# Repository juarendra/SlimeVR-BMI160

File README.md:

# SlimeVR-BMI160 DIY Tracker

**SlimeVR-BMI160** adalah proyek tracker full-body DIY (Do It Yourself) berbasis ESP32 dan sensor IMU BMI160, dikembangkan oleh [Positron Electronik](https://www.tokopedia.com/positronelectronic). Solusi ini merupakan alternatif hemat biaya dari tracker SlimeVR original, dengan tetap mempertahankan performa tinggi untuk pengalaman VR yang imersif.

## ⚡ Fitur Unggulan
- **Mikrokontroler**: ESP32-WROOM-32 (WiFi + BLE)
- **Sensor IMU**: BMI160 (header socket, mudah diganti)
- **Manajemen Daya**: USB-C atau LiPo 1S, charger TP4056 + proteksi DW01A
- **Konektor I2C**: Port ekspansi untuk sensor tambahan
- **LED Indikator**: 5 LED untuk status pengisian, koneksi, dan serial
- **Tombol**: Reset & power switch

## 🚀 Cara Penggunaan

### 📦 Isi Paket (untuk produk jadi)
- 1 Unit tracker SlimeVR-BMI160
- 1 Baterai LiPo (terpasang)

### 🔋 Pengisian Daya
- Colokkan USB-C: LED **biru** menyala saat mengisi, **merah** saat penuh.

### 🌐 Flash & Konfigurasi WiFi (Metode Termudah)
Gunakan **Web Installer** tanpa instalasi software:
1. Buka [SlimeVR BMI160 Web Installer](https://juarendra.github.io/SlimeVR-BMI160/) di Chrome/Edge (PC).
2. Hubungkan tracker via USB.
3. Klik **Install Firmware**, lalu masukkan SSID & Password WiFi.
4. Tunggu hingga proses selesai dan tracker terhubung ke server SlimeVR.

> **Catatan**: Web Installer menggunakan Web Serial, jadi pastikan browser mendukung (Chrome/Edge).

### 🛠️ Metode Manual (untuk Developer)
Jika Anda ingin mengembangkan atau mengompilasi firmware sendiri, ikuti panduan lengkap di:
➡️ **[Panduan Flashing Manual](./FIRMWARE/README.md)**

## 📂 Struktur Repositori
| Direktori | Isi |
|-----------|-----|
| `/PCB` | Desain PCB (EAGLE) dan file Gerber |
| `/HARDWARE` | Model 3D case (STL) dan dimensi |
| `/FIRMWARE` | Source code firmware (PlatformIO) dan file .bin compiled |
| `/site` | Web Installer (HTML, CSS, JS, manifest) |
| `/DOC` | Dokumentasi, gambar, BOM, datasheet |
| `/scripts` | Script otomatisasi (QA, release) |

## 🔧 Untuk Pengembang (DIY)
Jika Anda ingin merakit sendiri:
1. **Rakit Hardware**: Gunakan file PCB dari `/PCB/CAD-CAM`, BOM dari `/DOC/BOM_SlimeVRDiyModular.csv`, dan case 3D dari `/HARDWARE/case`.
2. **Flash Firmware**: Ikuti panduan di `/FIRMWARE/README.md`.
3. **Verifikasi**: Gunakan serial monitor untuk memastikan koneksi WiFi dan sensor.

## 🐛 Pemecahan Masalah Umum
- **Tracker tidak muncul di server**: Pastikan SSID/password benar, PC dan tracker satu jaringan, saklar ON.
- **LED mati total**: Cek saklar, charge baterai via USB-C.

## 📖 Dokumentasi Lengkap
- [Dokumentasi Software (PDF)](./DOC/SOFTWARE_USAGE.pdf) — panduan detail penggunaan web installer dan manual.

<details>
<summary><strong>📐 Detail Teknis dan Galeri</strong></summary>

| Fitur | Komponen |
|-------|----------|
| Mikrokontroler | ESP32-WROOM-32 |
| Sensor IMU | BMI160 |
| USB-to-Serial | FTDI FT231XS |
| Charger | TP4056 |
| Proteksi Baterai | DW01A + FS8205A |
| Regulator | M3406 (3.3V 800mA) |

**Diagram Pinout**:

**Dimensi Board**: [PDF](https://github.com/juarendra/SlimeVR-BMI160/blob/main/HARDWARE/dimension_SlimeVR.pdf)

**Galeri**:

</details>

## ❓ FAQ
*Segera hadir.*

## 🤝 Kontribusi
Pull request dan saran sangat diterima! Silakan buka issue di GitHub.

## 📜 Lisensi
MIT License © 2024 Positron Electronik

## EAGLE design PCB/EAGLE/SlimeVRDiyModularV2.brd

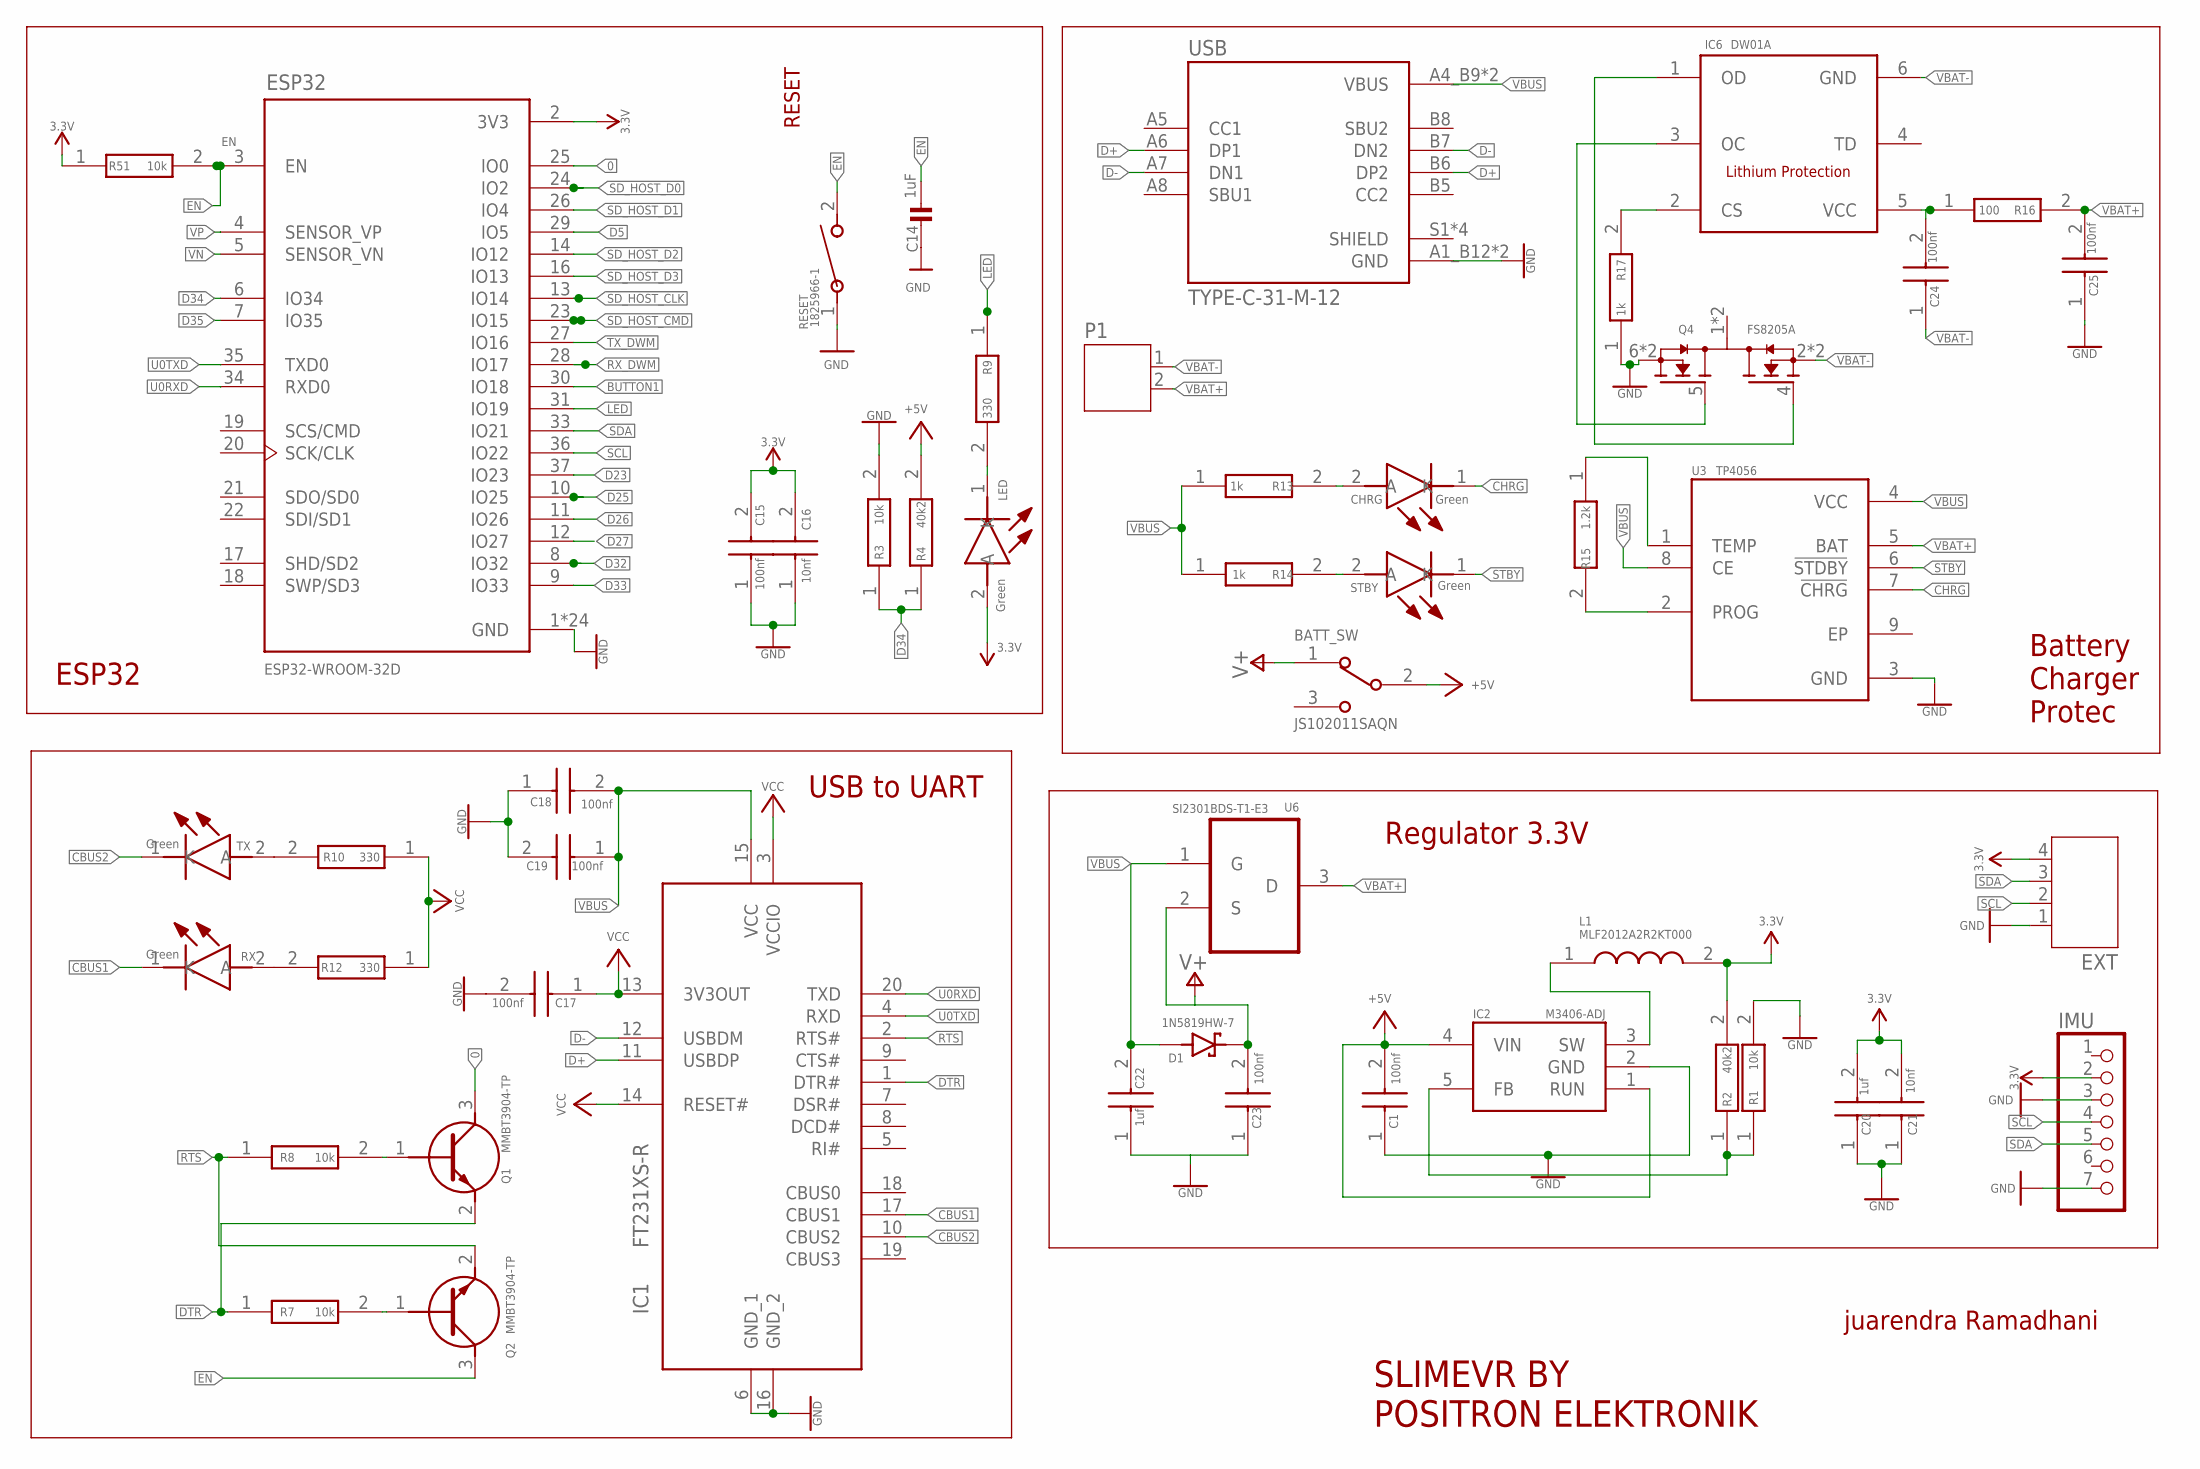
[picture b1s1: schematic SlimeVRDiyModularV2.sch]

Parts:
BATT_SW: JS102011SAQN; SW_JS102011SAQN
C1, C15, C17, C18, C19, C23, C24, C25: 100nf; CAPC1608X87N
C14: 1uF; 0603
C16, C21: 10nf; CAPC1608X87N
C20, C22: 1uf; CAPC1608X87N
CHRG: Green; LEDC2012X80N
D1: 1N5819HW-7; SOD3715X145N
ESP32: ESP32-WROOM-32D; MODULE_ESP32-WROOM-32D
EXT: JST-PH4
IC1: FT231XS-R; SOP64P599X175-20N
IC2: M3406-ADJ; SOT95P280X100-5N
IC6: DW01A; SOT23-6
IMU: PINHD-1X7; 1X07
L1: MLF2012A2R2KT000; INDC2012X105N
LED: Green; LEDC2012X80N
P1: JST-PH2
Q1, Q2: MMBT3904-TP; SI2305TP
Q4: FS8205A; SOP65P640X120-8N
R1, R3, R7, R8, R51: 10k; RESC1608X55N
R2, R4: 40k2; RESC1608X55N
R9, R10, R12: 330; ERJH3
R13, R14, R17: 1k; RESC1608X55N
R15: 1.2k; RESC1608X55N
R16: 100; RESC1608X55N
RESET: 1825966-1; SWDIP2_256X170P100
RX: Green; LEDC2012X80N
STBY: Green; LEDC2012X80N
TX: Green; LEDC2012X80N
U3: TP4056; SOP127P600X175-9N
U6: SI2301BDS-T1-E3; SOT95P237X112-3N
USB: TYPE-C-31-M-12; HRO_TYPE-C-31-M-12

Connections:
0: ESP32.25 (IO0), Q1.3 (C)
3.3V: C15.2, C16.2, C20.2, C21.2, ESP32.2 (3V3), EXT.4, IMU.2, L1.2, LED.2 (A), R2.2, R51.1
+5V: BATT_SW.2, C1.2, IC2.1 (RUN), IC2.4 (VIN), R4.2
BUTTON1: ESP32.30 (IO18)
CBUS1: IC1.17 (CBUS1), RX.1 (K)
CBUS2: IC1.10 (CBUS2), TX.1 (K)
CHRG: CHRG.1 (K), U3.7 (!CHRG)
D5: ESP32.29 (IO5)
D23: ESP32.37 (IO23)
D25: ESP32.10 (IO25)
D26: ESP32.11 (IO26)
D27: ESP32.12 (IO27)
D32: ESP32.8 (IO32)
D33: ESP32.9 (IO33)
D34: ESP32.6 (IO34), R3.1, R4.1
D35: ESP32.7 (IO35)
D+: IC1.11 (USBDP), USB.A6 (DP1), USB.B6 (DP2)
D-: IC1.12 (USBDM), USB.A7 (DN1), USB.B7 (DN2)
DTR: IC1.1 (DTR#), Q1.2 (E), R7.1
EN: C14.1, ESP32.3 (EN), Q2.3 (C), R51.2, RESET.2
GND: C1.1, C14.2, C15.1, C16.1, C17.2, C18.1, C19.2, C20.1, C21.1, C22.1, C23.1, C25.1, ESP32.1 (GND), ESP32.15 (GND), ESP32.38 (GND), ESP32.39_1 (GND), ESP32.39_2 (GND), ESP32.39_3 (GND), ESP32.39_4 (GND), ESP32.39_5 (GND), ESP32.39_6 (GND), ESP32.39_7 (GND), ESP32.39_8 (GND), ESP32.39_9 (GND), ESP32.39_10 (GND), ESP32.39_11 (GND), ESP32.39_12 (GND), ESP32.39_13 (GND), ESP32.39_14 (GND), ESP32.39_15 (GND), ESP32.39_16 (GND), ESP32.39_17 (GND), ESP32.39_18 (GND), ESP32.39_19 (GND), ESP32.39_20 (GND), ESP32.39_21 (GND), EXT.1, IC1.6 (GND_1), IC1.16 (GND_2), IC2.2 (GND), IMU.3, IMU.7, Q4.6 (S2), Q4.7 (S2), R1.2, R3.2, R17.1, RESET.1, U3.3 (GND), USB.A1_B12 (GND), USB.B1_A12 (GND)
LED: ESP32.31 (IO19), R9.1
unnamed: IC2.3 (SW), L1.1
unnamed: LED.1 (K), R9.2
unnamed: IC2.5 (FB), R1.1, R2.1
unnamed: Q2.1 (B), R7.2
unnamed: Q1.1 (B), R8.2
unnamed: R12.2, RX.2 (A)
unnamed: R10.2, TX.2 (A)
unnamed: CHRG.2 (A), R13.2
unnamed: R14.2, STBY.2 (A)
unnamed: R15.1, U3.1 (TEMP)
unnamed: R15.2, U3.2 (PROG)
unnamed: C24.2, IC6.5 (VCC), R16.1
unnamed: IC6.1 (OD), Q4.4 (G1)
unnamed: IC6.2 (CS), R17.2
unnamed: IC6.3 (OC), Q4.5 (G2)
RTS: IC1.2 (RTS#), Q2.2 (E), R8.1
RX_DWM: ESP32.28 (IO17)
SCL: ESP32.36 (IO22), EXT.2, IMU.4
SDA: ESP32.33 (IO21), EXT.3, IMU.5
SD_HOST_CLK: ESP32.13 (IO14)
SD_HOST_CMD: ESP32.23 (IO15)
SD_HOST_D0: ESP32.24 (IO2)
SD_HOST_D1: ESP32.26 (IO4)
SD_HOST_D2: ESP32.14 (IO12)
SD_HOST_D3: ESP32.16 (IO13)
STBY: STBY.1 (K), U3.6 (!STDBY)
TX_DWM: ESP32.27 (IO16)
U0RXD: ESP32.34 (RXD0), IC1.20 (TXD)
U0TXD: ESP32.35 (TXD0), IC1.4 (RXD)
V+: BATT_SW.1, C23.2, D1.C (K), U6.2 (S)
VBAT+: C25.2, P1.2, R16.2, U3.5 (BAT), U6.3 (D)
VBAT-: C24.1, IC6.6 (GND), P1.1, Q4.2 (S1), Q4.3 (S1)
VBUS: C18.2, C19.1, C22.2, D1.A, IC1.15 (VCC), R13.1, R14.1, U3.4 (VCC), U3.8 (CE), U6.1 (G), USB.A4_B9 (VBUS), USB.B4_A9 (VBUS)
VCC: C17.1, IC1.3 (VCCIO), IC1.13 (3V3OUT), IC1.14 (RESET#), R10.1, R12.1
VN: ESP32.5 (SENSOR_VN)
VP: ESP32.4 (SENSOR_VP)

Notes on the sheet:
RESET
ESP32
USB to UART
Battery Charger Protec
Regulator 3.3V
SLIMEVR BY POSITRON ELEKTRONIK
juarendra Ramadhani

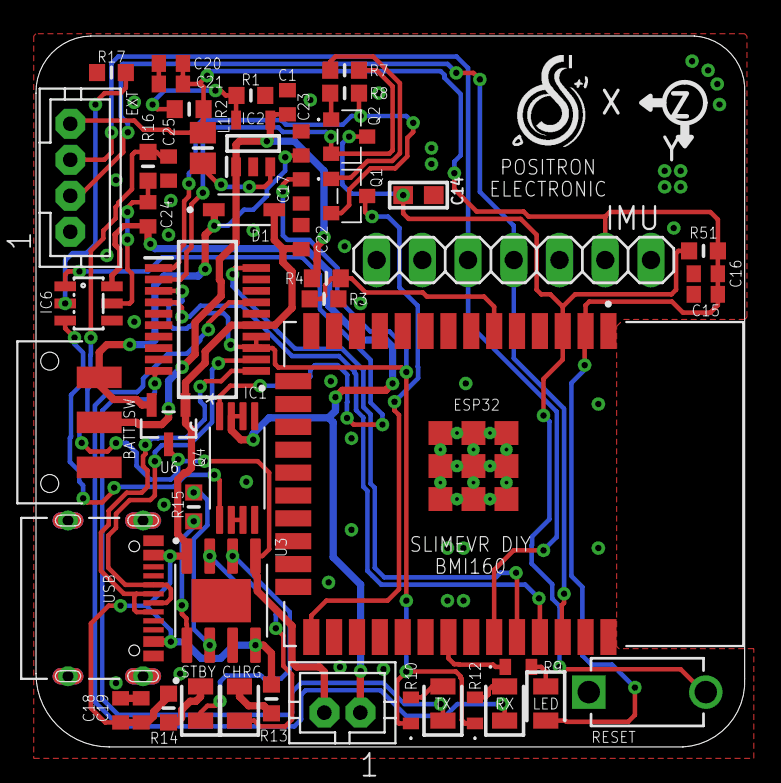
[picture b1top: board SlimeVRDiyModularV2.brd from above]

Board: 2 copper layers, 39.4 x 39.5 mm, 50 parts (0 on the bottom side), 39 nets.

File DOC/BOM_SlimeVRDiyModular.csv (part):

"Qty";"Value";"Device";"Package";"Parts";"Description";"AVAILABILITY";"BUILT_BY";"CATEGORY";"CHECK_PRICES";"COPYRIGHT";"DESCRIPTION";"DIGIKEY_PARTNUMBER";"DIGIKEY_PRICE-STOCK";"HEIGHT";"LCSC_PART_NUMBER";"LCSC_PRICE-STOCK";"MANUFACTURER_NAME";"MANUFACTURER_PART_NUMBER";"MF";"MOUSER_PART_NUMBER";"MOUSER_PRICE-STOCK";"MP";"PACKAGE";"PART_STATUS";"POPULARITY";"PRICE";"PURCHASE-URL";"SERIES";"SNAPEDA_LINK";"VALUE";"VENDOR";
"1";"";"JST-PH2";"JST-PH2";"P1";"";"";"";"";"";"";"";"";"";"";"";"";"";"";"";"";"";"";"";"";"";"";"";"";"";"";"";
"1";"";"JST-PH4";"JST-PH4";"EXT";"";"";"";"";"";"";"";"";"";"";"";"";"";"";"";"";"";"";"";"";"";"";"";"";"";"";"";
"1";"";"PINHD-1X7";"1X07";"IMU";"PIN HEADER";"";"";"";"";"";"";"";"";"";"";"";"";"";"";"";"";"";"";"";"0";"";"";"";"";"";"";
"1";"1.2k";"ESR03EZPJ102";"RESC1608X55N";"R15";"Thick Film Resistors - SMD 0603 1Kohm 5% Anti Surge AEC-Q200";"";"";"";"";"";"Thick Film Resistors - SMD 0603 1Kohm 5% Anti Surge AEC-Q200";"RHM1.0KDCT-ND";"https://www.digikey.com/product-detail/en/rohm-semiconductor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";"0.55mm";"";"";"ROHM Semiconductor";"ESR03EZPJ102";"";"755-ESR03EZPJ102";"https://www.mouser.co.uk/ProductDetail/ROHM-Semiconductor/ES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";"";"";"";"";"";"";"";"";"1k";"";
"1";"100";"ESR03EZPJ102";"RESC1608X55N";"R16";"Thick Film Resistors - SMD 0603 1Kohm 5% Anti Surge AEC-Q200";"";"";"";"";"";"Thick Film Resistors - SMD 0603 1Kohm 5% Anti Surge AEC-Q200";"RHM1.0KDCT-ND";"https://www.digikey.com/product-detail/en/rohm-semiconductor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";"0.55mm";"";"";"ROHM Semiconductor";"ESR03EZPJ102";"";"755-ESR03EZPJ102";"https://www.mouser.co.uk/ProductDetail/ROHM-Semiconductor/ES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";"";"";"";"";"";"";"";"";"1k";"";
"8";"100nf";"885012206071";"CAPC1608X87N";"C1, C15, C17, C18, C19, C23, C24, C25";"Wurth Elektronik 0603 WCAP-CSGP 100nF Ceramic Multilayer Capacitor, 25 V dc, +125C, X7R Dielectric, +/-10%";"";"";"";"";"";"Wurth Elektronik 0603 WCAP-CSGP 100nF Ceramic Multilayer Capacitor, 25 V dc, +125C, X7R Dielectric, +/-10%";"732-7989-1-ND";"https://www.digikey.com/product-detail/en/w%C3%BCrth-elektro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";"0.87mm";"";"";"Wurth Elektronik";"885012206071";"";"710-885012206071";"https://www.mouser.co.uk/ProductDetail/Wurth-Elektronik/8850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";"";"";"";"";"";"";"";"";"100nf";"";
"5";"10k";"ESR03EZPJ103";"RESC1608X55N";"R1, R3, R7, R8, R51";"Thick Film Resistors - SMD 0603 10Kohm 5% Anti Surge AEC-Q200";"";"";"";"";"";"Thick Film Resistors - SMD 0603 10Kohm 5% Anti Surge AEC-Q200";"RHM10KDCT-ND";"https://www.digikey.com/product-detail/en/rohm-semiconductor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";"0.55mm";"";"";"ROHM Semiconductor";"ESR03EZPJ103";"";"755-ESR03EZPJ103";"https://www.mouser.com/Search/Refine.aspx?Keyword=755-ESR03EZPJ103";"";"";"";"";"";"";"";"";"10k";"";
"2";"10nf";"885012206089";"CAPC1608X87N";"C16, C21";"Wurth Elektronik 0603 WCAP-CSGP 10nF Ceramic Multilayer Capacitor, 50 V dc, +125C, X7R Dielectric, +/-10%";"";"";"";"";"";"Wurth Elektronik 0603 WCAP-CSGP 10nF Ceramic Multilayer Capacitor, 50 V dc, +125C, X7R Dielectric, +/-10%";"732-8007-1-ND";"https://www.digikey.com/product-detail/en/w%C3%BCrth-elektro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";"0.87mm";"";"";"Wurth Elektronik";"885012206089";"";"710-885012206089";"https://www.mouser.co.uk/ProductDetail/Wurth-Elektronik/8850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";"";"";"";"";"";"";"";"";"10nf";"";
"1";"1825966-1";"1825966-1";"SWDIP2_256X170P100";"RESET";"";"";"EMA_UL_Team";"Tactile Switches";"";"Copyright (C) 2016 Accelerated Designs. All rights reserved";"FSMCH=3.5 X 6.0 X 4.3 TACT SWITCH, HT";"";"";"";"";"";"";"1825966-1";"";"";"";"";"";"active";"";"";"";"Unknown";"";"";"TE Connectivity";
"1";"1N5819HW-7";"1N5819HW-7";"SOD3715X145N";"D1";"1N5819HW Series 40 V 1 A Surface Mount Schottky Barrier Rectifier - SOD-123  Check availability";"In Stock";"";"";"https://www.snapeda.com/parts/1N5819HW-7/Diodes+Inc./view-pa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";"";" Diode Schottky 40 V 1A Surface Mount SOD-123 ";"";"";"";"";"";"";"";"Diodes Inc.";"";"";"1N5819HW-7";"SOD-123 Fairchild Semiconductor";"";"";"None";"https://www.snapeda.com/api/url_track_click_mouser/?unipart_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 Inc.&part_name=1N5819HW-7&search_term=1n5819 ";"";"https://www.snapeda.com/parts/1N5819HW-7/Diodes+Inc./view-pa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";"";"";
"3";"1k";"ESR03EZPJ102";"RESC1608X55N";"R13, R14, R17";"Thick Film Resistors - SMD 0603 1Kohm 5% Anti Surge AEC-Q200";"";"";"";"";"";"Thick Film Resistors - SMD 0603 1Kohm 5% Anti Surge AEC-Q200";"RHM1.0KDCT-ND";"https://www.digikey.com/product-detail/en/rohm-semiconductor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";"0.55mm";"";"";"ROHM Semiconductor";"ESR03EZPJ102";"";"755-ESR03EZPJ102";"https://www.mouser.co.uk/ProductDetail/ROHM-Semiconductor/ES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";"";"";"";"";"";"";"";"";"1k";"";
"1";"1uF";"CAP_CERAMIC0603";"0603";"C14";"Ceramic Capacitors";"";"";"";"";"";"";"";"";"";"";"";"";"";"";"";"";"";"";"";"";"";"";"";"";"";"";
"2";"1uf";"885012206071";"CAPC1608X87N";"C20, C22";"Wurth Elektronik 0603 WCAP-CSGP 100nF Ceramic Multilayer Capacitor, 25 V dc, +125C, X7R Dielectric, +/-10%";"";"";"";"";"";"Wurth Elektronik 0603 WCAP-CSGP 100nF Ceramic Multilayer Capacitor, 25 V dc, +125C, X7R Dielectric, +/-10%";"732-7989-1-ND";"https://www.digikey.com/product-detail/en/w%C3%BCrth-elektro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";"0.87mm";"";"";"Wurth Elektronik";"885012206071";"";"710-885012206071";"https://www.mouser.co.uk/ProductDetail/Wurth-Elektronik/8850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";"";"";"";"";"";"";"";"";"100nf";"";
"3";"330";"ERJ-H3EF3300V";"ERJH3";"R9, R10, R12";"Power Rating 0.125W,Resistance 330 Ohm,LxW(EIA) 1.6 x 0.8 (EIA:0603) mm";"";"";"";"";"";"Power Rating 0.125W,Resistance 330 Ohm,LxW(EIA) 1.6 x 0.8 (EIA:0603) mm";"";"";"mm";"";"";"Panasonic";"ERJ-H3EF3300V";"";"667-ERJ-H3EF3300V";"https://www.mouser.co.uk/ProductDetail/Panasonic/ERJ-H3EF330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";"";"";"";"";"";"";"";"";"330";"";
"2";"40k2";"ERJ-S03F4022V";"RESC1608X55N";"R2, R4";"Thick Film Resistors - SMD 0603 40.2Kohms 1% Anti-Sulfur";"";"";"";"";"";"Thick Film Resistors - SMD 0603 40.2Kohms 1% Anti-Sulfur";"";"";"0.55mm";"";"";"Panasonic";"ERJ-S03F4022V";"";"667-ERJ-S03F4022V";"https://www.mouser.com/Search/Refine.aspx?Keyword=667-ERJ-S03F4022V";"";"";"";"";"";"";"";"";"";"";
"1";"DW01A";"DW01A";"SOT23-6";"IC6";"Check availability";"Not in stock";"";"";"https://www.snapeda.com/parts/DW01A/Fortune+Semiconductor/vi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";"";" One Cell Lithium-ion/Polymer Battery Protection IC ";"";"";"";"";"";"";"";"Fortune Semiconductor";"";"";"DW01A";"SOT-23-6 Fortune Semiconductor";"";"";"None";"";"";"https://www.snapeda.com/parts/DW01A/Fortune+Semiconductor/vi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";"";"";
"1";"ESP32-WROOM-32D";"ESP32-WROOM-32D";"MODULE_ESP32-WROOM-32D";"ESP32";"Bluetooth, WiFi 802.11b/g/n, Bluetooth v4.2 + EDR, Class 1, 2 and 3 Transceiver Module 2.4GHz ~ 2.5GHz Integrated, Trace Surface Mount Check availability";"In Stock";"";"";"";"";" Bluetooth, WiFi 802.11b/g/n, Bluetooth v4.2 +EDR, Class 1, 2 and 3 Transceiver Module 2.4GHz ~ 2.5GHz Integrated ";"";"";"";"";"";"";"";"Espressif Systems";"";"";"ESP32-WROOM-32D";"Module Espressif Systems";"";"";"None";"https://pricing.snapeda.com/search/part/ESP32-WROOM-32D/?ref=eda";"";"";"";"";
"1";"FS8205A";"FS8205A";"SOP65P640X120-8N";"Q4";"N/A Check availability";"Not in stock";"";"";"https://www.snapeda.com/parts/FS8205A/Fortune+Semiconductor/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";"";" ";"";"";"";"";"";"";"";"Fortune Semiconductor";"";"";"FS8205A";"Package ";"";"";"None";"";"";"https://www.snapeda.com/parts/FS8205A/Fortune+Semiconductor/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";"";"";
"1";"FT231XS-R";"FT231XS-R";"SOP64P599X175-20N";"IC1";"FTDI Chip FT231XS-R, Interface RS232, RS422, RS485, SIE, UART 3MBd, 5 V, 20-pin, SSOP";"";"";"";"";"";"FTDI Chip FT231XS-R, Interface RS232, RS422, RS485, SIE, UART 3MBd, 5 V, 20-pin, SSOP";"";"";"1.753mm";"";"";"FTDI Chip";"FT231XS-R";"";"895-FT231XS-R";"https://www.mouser.co.uk/ProductDetail/FTDI/FT231XS-R?qs=Gp1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";"";"";"";"";"";"";"";"";"";"";
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
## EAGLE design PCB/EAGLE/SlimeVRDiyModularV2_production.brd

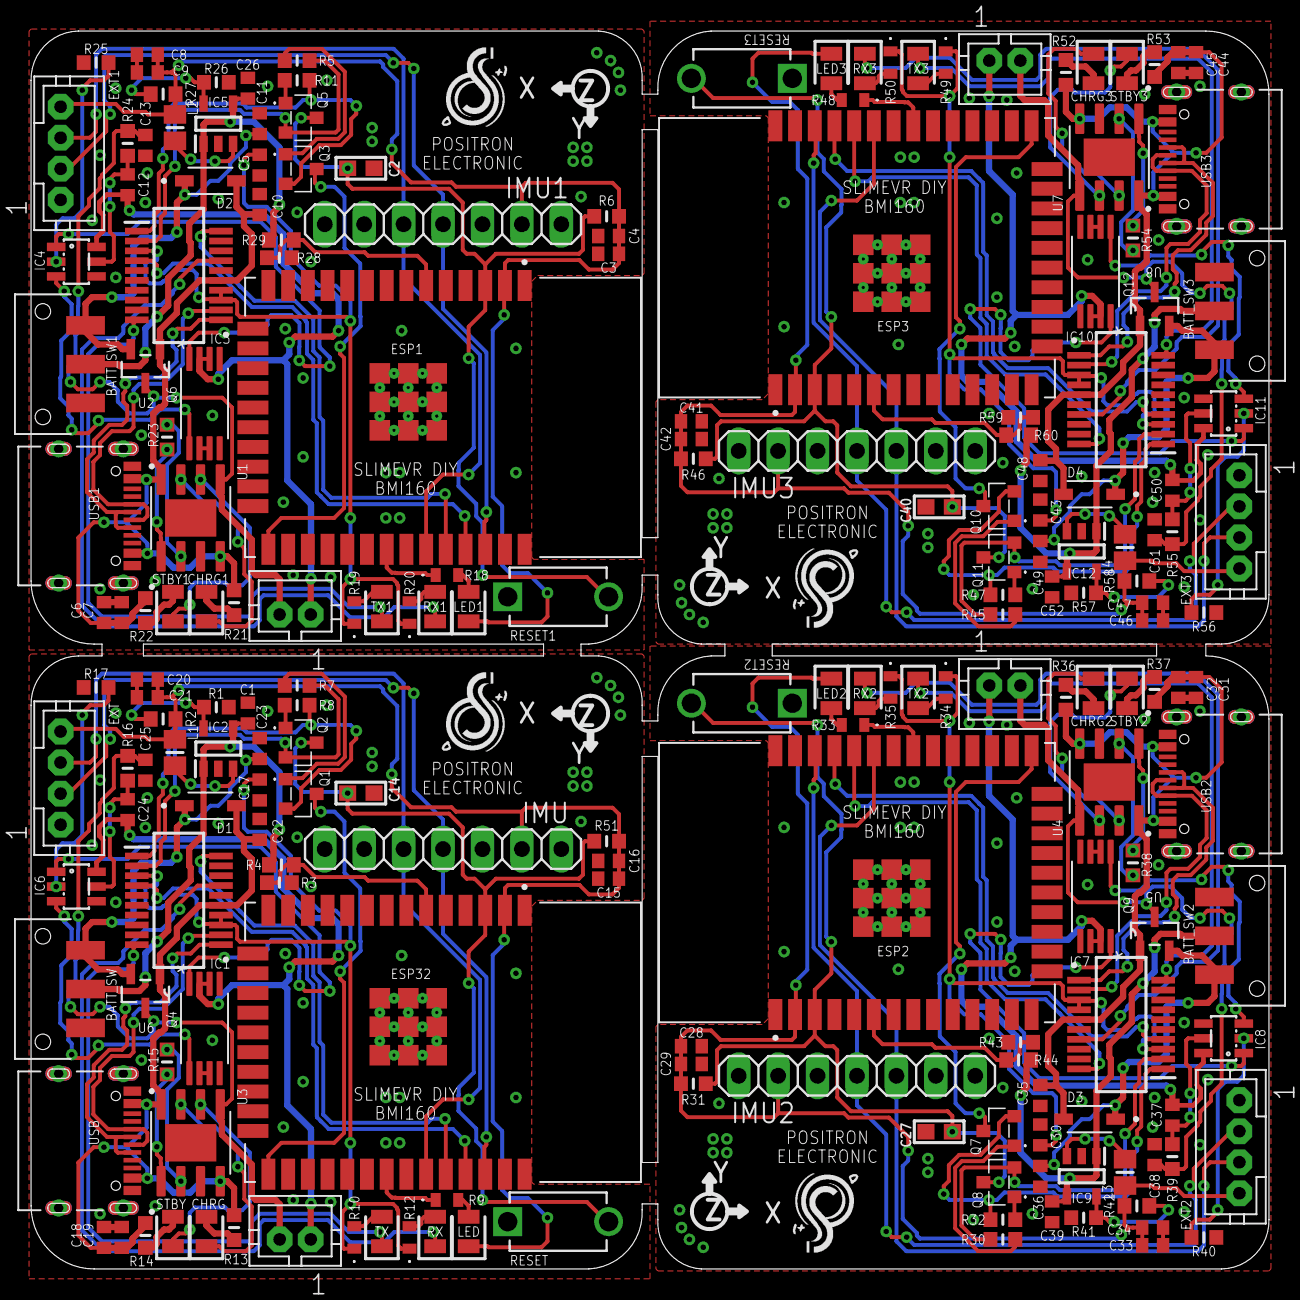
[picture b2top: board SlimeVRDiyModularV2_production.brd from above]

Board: 2 copper layers, 79.8 x 79.8 mm, 200 parts (0 on the bottom side), 156 nets.

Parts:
BATT_SW, BATT_SW1, BATT_SW2, BATT_SW3: JS102011SAQN; SW_JS102011SAQN
C1, C3, C5, C6, C7, C11, C12, C13, C15, C17, C18, C19, C23, C24, C25, C26, C28, C30, C31, C32, C36, C37, C38, C39, C41, C43, C44, C45, C49, C50, C51, C52: 100nf; CAPC1608X87N
C2, C14, C27, C40: 1uF; 0603
C4, C9, C16, C21, C29, C34, C42, C47: 10nf; CAPC1608X87N
C8, C10, C20, C22, C33, C35, C46, C48: 1uf; CAPC1608X87N
CHRG, CHRG1, CHRG2, CHRG3: Green; LEDC2012X80N
D1, D2, D3, D4: 1N5819HW-7; SOD3715X145N
ESP1, ESP2, ESP3, ESP32: ESP32-WROOM-32D; MODULE_ESP32-WROOM-32D
EXT, EXT1, EXT2, EXT3: JST-PH4
IC1, IC3, IC7, IC10: FT231XS-R; SOP64P599X175-20N
IC2, IC5, IC9, IC12: M3406-ADJ; SOT95P280X100-5N
IC4, IC6, IC8, IC11: DW01A; SOT23-6
IMU, IMU1, IMU2, IMU3: 1X07
L1, L2, L3, L4: MLF2012A2R2KT000; INDC2012X105N
LED, LED1, LED2, LED3: Green; LEDC2012X80N
P1, P2, P3, P4: JST-PH2
Q1, Q2, Q3, Q5, Q7, Q8, Q10, Q11: MMBT3904-TP; SI2305TP
Q4, Q6, Q9, Q12: FS8205A; SOP65P640X120-8N
R1, R3, R5, R6, R7, R8, R11, R26, R28, R30, R31, R32, R41, R43, R45, R46, R47, R51, R57, R59: 10k; RESC1608X55N
R2, R4, R27, R29, R42, R44, R58, R60: 40k2; RESC1608X55N
R9, R10, R12, R18, R19, R20, R33, R34, R35, R48, R49, R50: 330; ERJH3
R13, R14, R17, R21, R22, R25, R36, R37, R40, R52, R53, R56: 1k; RESC1608X55N
R15, R23, R38, R54: 1.2k; RESC1608X55N
R16, R24, R39, R55: 100; RESC1608X55N
RESET, RESET1, RESET2, RESET3: 1825966-1; SWDIP2_256X170P100
RX, RX1, RX2, RX3: Green; LEDC2012X80N
STBY, STBY1, STBY2, STBY3: Green; LEDC2012X80N
TX, TX1, TX2, TX3: Green; LEDC2012X80N
U1, U3, U4, U7: TP4056; SOP127P600X175-9N
U2, U5, U6, U8: SI2301BDS-T1-E3; SOT95P237X112-3N
USB, USB1, USB2, USB3: TYPE-C-31-M-12; HRO_TYPE-C-31-M-12

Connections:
0: ESP32.25, Q1.3
1: ESP1.25, Q3.3
2: ESP2.25, Q7.3
3: ESP3.25, Q10.3
3.3V: C15.2, C16.2, C20.2, C21.2, ESP32.2, EXT.4, IMU.2, L1.2, LED.1, R2.2, R51.1
3.3V1: C3.2, C4.2, C8.2, C9.2, ESP1.2, EXT1.4, IMU1.2, L2.2, LED1.1, R6.1, R27.2
3.3V2: C28.2, C29.2, C33.2, C34.2, ESP2.2, EXT2.4, IMU2.2, L3.2, LED2.1, R31.1, R42.2
3.3V3: C41.2, C42.2, C46.2, C47.2, ESP3.2, EXT3.4, IMU3.2, L4.2, LED3.1, R46.1, R58.2
+5V: BATT_SW.2, C1.2, IC2.1, IC2.4, R4.2
+5V1: BATT_SW1.2, C26.2, IC5.1, IC5.4, R29.2
+5V2: BATT_SW2.2, C39.2, IC9.1, IC9.4, R44.2
+5V3: BATT_SW3.2, C52.2, IC12.1, IC12.4, R60.2
CBUS1: IC1.17, RX.1
CBUS2: IC1.10, TX.1
CBUS3: IC3.17, RX1.1
CBUS4: IC3.10, TX1.1
CBUS5: IC7.17, RX2.1
CBUS6: IC7.10, TX2.1
CBUS7: IC10.17, RX3.1
CBUS8: IC10.10, TX3.1
CHRG: CHRG.1, U3.7
CHRG1: CHRG1.1, U1.7
CHRG2: CHRG2.1, U4.7
CHRG3: CHRG3.1, U7.7
D1: ESP1.6, R28.1, R29.1
D11: ESP2.6, R43.1, R44.1
D20: ESP3.6, R59.1, R60.1
D34: ESP32.6, R3.1, R4.1
D+: IC1.11, USB.A6, USB.B6
D+1: IC3.11, USB1.A6, USB1.B6
D+2: IC7.11, USB2.A6, USB2.B6
D+3: IC10.11, USB3.A6, USB3.B6
D-: IC1.12, USB.A7, USB.B7
D-1: IC3.12, USB1.A7, USB1.B7
D-2: IC7.12, USB2.A7, USB2.B7
D-3: IC10.12, USB3.A7, USB3.B7
DTR: IC1.1, Q1.2, R7.1
DTR1: IC3.1, Q3.2, R5.1
DTR2: IC7.1, Q7.2, R30.1
DTR3: IC10.1, Q10.2, R45.1
EN: C14.1, ESP32.3, Q2.3, R51.2, RESET.2
EN1: C2.1, ESP1.3, Q5.3, R6.2, RESET1.2
EN2: C27.1, ESP2.3, Q8.3, R31.2, RESET2.2
EN3: C40.1, ESP3.3, Q11.3, R46.2, RESET3.2
GND: C1.1, C14.2, C15.1, C16.1, C17.2, C18.1, C19.2, C20.1, C21.1, C22.1, C23.1, C25.1, ESP32.1, ESP32.15, ESP32.38, ESP32.39_1, ESP32.39_2, ESP32.39_3, ESP32.39_4, ESP32.39_5, ESP32.39_6, ESP32.39_7, ESP32.39_8, ESP32.39_9, ESP32.39_10, ESP32.39_11, ESP32.39_12, ESP32.39_13, ESP32.39_14, ESP32.39_15, ESP32.39_16, ESP32.39_17, ESP32.39_18, ESP32.39_19, ESP32.39_20, ESP32.39_21, EXT.1, IC1.6, IC1.16, IC2.2, IMU.3, IMU.7, Q4.6, Q4.7, R1.2, R3.2, R17.1, RESET.1, U3.3, USB.A1_B12, USB.B1_A12
GND1: C2.2, C3.1, C4.1, C5.2, C6.1, C7.2, C8.1, C9.1, C10.1, C11.1, C13.1, C26.1, ESP1.1, ESP1.15, ESP1.38, ESP1.39_1, ESP1.39_2, ESP1.39_3, ESP1.39_4, ESP1.39_5, ESP1.39_6, ESP1.39_7, ESP1.39_8, ESP1.39_9, ESP1.39_10, ESP1.39_11, ESP1.39_12, ESP1.39_13, ESP1.39_14, ESP1.39_15, ESP1.39_16, ESP1.39_17, ESP1.39_18, ESP1.39_19, ESP1.39_20, ESP1.39_21, EXT1.1, IC3.6, IC3.16, IC5.2, IMU1.3, IMU1.7, Q6.6, Q6.7, R25.1, R26.2, R28.2, RESET1.1, U1.3, USB1.A1_B12, USB1.B1_A12
GND2: C27.2, C28.1, C29.1, C30.2, C31.1, C32.2, C33.1, C34.1, C35.1, C36.1, C38.1, C39.1, ESP2.1, ESP2.15, ESP2.38, ESP2.39_1, ESP2.39_2, ESP2.39_3, ESP2.39_4, ESP2.39_5, ESP2.39_6, ESP2.39_7, ESP2.39_8, ESP2.39_9, ESP2.39_10, ESP2.39_11, ESP2.39_12, ESP2.39_13, ESP2.39_14, ESP2.39_15, ESP2.39_16, ESP2.39_17, ESP2.39_18, ESP2.39_19, ESP2.39_20, ESP2.39_21, EXT2.1, IC7.6, IC7.16, IC9.2, IMU2.3, IMU2.7, Q9.6, Q9.7, R40.1, R41.2, R43.2, RESET2.1, U4.3, USB2.A1_B12, USB2.B1_A12
GND3: C40.2, C41.1, C42.1, C43.2, C44.1, C45.2, C46.1, C47.1, C48.1, C49.1, C51.1, C52.1, ESP3.1, ESP3.15, ESP3.38, ESP3.39_1, ESP3.39_2, ESP3.39_3, ESP3.39_4, ESP3.39_5, ESP3.39_6, ESP3.39_7, ESP3.39_8, ESP3.39_9, ESP3.39_10, ESP3.39_11, ESP3.39_12, ESP3.39_13, ESP3.39_14, ESP3.39_15, ESP3.39_16, ESP3.39_17, ESP3.39_18, ESP3.39_19, ESP3.39_20, ESP3.39_21, EXT3.1, IC10.6, IC10.16, IC12.2, IMU3.3, IMU3.7, Q12.6, Q12.7, R56.1, R57.2, R59.2, RESET3.1, U7.3, USB3.A1_B12, USB3.B1_A12
LED: ESP32.31, R9.1
LED1: ESP1.31, R18.1
LED2: ESP2.31, R33.1
LED3: ESP3.31, R48.1
unnamed: IC2.3, L1.1
unnamed: Q5.1, R5.2
unnamed: IC2.5, R1.1, R2.1
unnamed: Q3.1, R11.2
unnamed: R20.2, RX1.2
unnamed: R19.2, TX1.2
unnamed: CHRG1.2, R21.2
unnamed: R22.2, STBY1.2
unnamed: Q2.1, R7.2
unnamed: R23.1, U1.1
unnamed: Q1.1, R8.2
unnamed: R12.2, RX.2
unnamed: R10.2, TX.2
unnamed: R23.2, U1.2
unnamed: CHRG.2, R13.2
unnamed: R14.2, STBY.2
unnamed: R15.1, U3.1
unnamed: R15.2, U3.2
unnamed: C24.2, IC6.5, R16.1
unnamed: IC6.1, Q4.4
unnamed: IC6.2, R17.2
unnamed: C12.2, IC4.5, R24.1
unnamed: IC4.1, Q6.4
unnamed: IC4.2, R25.2
unnamed: IC4.3, Q6.5
unnamed: IC6.3, Q4.5
unnamed: LED.2, R9.2
unnamed: LED1.2, R18.2
unnamed: IC5.3, L2.1
unnamed: IC5.5, R26.1, R27.1
unnamed: Q8.1, R30.2
unnamed: Q7.1, R32.2
unnamed: R35.2, RX2.2
unnamed: R34.2, TX2.2
unnamed: CHRG2.2, R36.2
unnamed: R37.2, STBY2.2
unnamed: R38.1, U4.1
unnamed: R38.2, U4.2
unnamed: C37.2, IC8.5, R39.1
unnamed: IC8.1, Q9.4
unnamed: IC8.2, R40.2
unnamed: IC8.3, Q9.5
unnamed: LED2.2, R33.2
unnamed: IC9.3, L3.1
unnamed: IC9.5, R41.1, R42.1
unnamed: Q11.1, R45.2
unnamed: Q10.1, R47.2
unnamed: R50.2, RX3.2
unnamed: R49.2, TX3.2
unnamed: CHRG3.2, R52.2
unnamed: R53.2, STBY3.2
unnamed: R54.1, U7.1
unnamed: R54.2, U7.2
unnamed: C50.2, IC11.5, R55.1
unnamed: IC11.1, Q12.4
unnamed: IC11.2, R56.2
unnamed: IC11.3, Q12.5
unnamed: LED3.2, R48.2
unnamed: IC12.3, L4.1
unnamed: IC12.5, R57.1, R58.1
RTS: IC1.2, Q2.2, R8.1
RTS1: IC3.2, Q5.2, R11.1
RTS2: IC7.2, Q8.2, R32.1
RTS3: IC10.2, Q11.2, R47.1
SCL: ESP32.36, EXT.2, IMU.4
SCL1: ESP1.36, EXT1.2, IMU1.4
SCL2: ESP2.36, EXT2.2, IMU2.4
SCL3: ESP3.36, EXT3.2, IMU3.4
SDA: ESP32.33, EXT.3, IMU.5
SDA1: ESP1.33, EXT1.3, IMU1.5
SDA2: ESP2.33, EXT2.3, IMU2.5
SDA3: ESP3.33, EXT3.3, IMU3.5
STBY: STBY.1, U3.6
STBY1: STBY1.1, U1.6
STBY2: STBY2.1, U4.6
STBY3: STBY3.1, U7.6
U0RXD: ESP32.34, IC1.20
U0RXD1: ESP1.34, IC3.20
U0RXD2: ESP2.34, IC7.20
U0RXD3: ESP3.34, IC10.20
U0TXD: ESP32.35, IC1.4
U0TXD1: ESP1.35, IC3.4
U0TXD2: ESP2.35, IC7.4
U0TXD3: ESP3.35, IC10.4
V+: BATT_SW.1, C23.2, D1.C, U6.2
V+1: BATT_SW1.1, C11.2, D2.C, U2.2
V+2: BATT_SW2.1, C36.2, D3.C, U5.2
V+3: BATT_SW3.1, C49.2, D4.C, U8.2
VBAT+: C25.2, P1.2, R16.2, U3.5, U6.3
VBAT+1: C13.2, P2.2, R24.2, U1.5, U2.3
VBAT+2: C38.2, P3.2, R39.2, U4.5, U5.3
VBAT+3: C51.2, P4.2, R55.2, U7.5, U8.3
VBAT-: C24.1, IC6.6, P1.1, Q4.2, Q4.3
VBAT-1: C12.1, IC4.6, P2.1, Q6.2, Q6.3
VBAT-2: C37.1, IC8.6, P3.1, Q9.2, Q9.3
VBAT-3: C50.1, IC11.6, P4.1, Q12.2, Q12.3
VBUS: C18.2, C19.1, C22.2, D1.A, IC1.15, R13.1, R14.1, U3.4, U3.8, U6.1, USB.A4_B9, USB.B4_A9
VBUS1: C6.2, C7.1, C10.2, D2.A, IC3.15, R21.1, R22.1, U1.4, U1.8, U2.1, USB1.A4_B9, USB1.B4_A9
VBUS2: C31.2, C32.1, C35.2, D3.A, IC7.15, R36.1, R37.1, U4.4, U4.8, U5.1, USB2.A4_B9, USB2.B4_A9
VBUS3: C44.2, C45.1, C48.2, D4.A, IC10.15, R52.1, R53.1, U7.4, U7.8, U8.1, USB3.A4_B9, USB3.B4_A9
VCC: C17.1, IC1.3, IC1.13, IC1.14, R10.1, R12.1
VCC1: C5.1, IC3.3, IC3.13, IC3.14, R19.1, R20.1
VCC2: C30.1, IC7.3, IC7.13, IC7.14, R34.1, R35.1
VCC3: C43.1, IC10.3, IC10.13, IC10.14, R49.1, R50.1

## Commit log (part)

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2024-05-29 FEAT: update finish rev1 on board
2024-05-30 FEAT: update 3D model, gerber and BOM
2024-05-31 DOC: add Dimesion and SCH
2024-06-18 FIX: fix problem on pcb
2024-06-28 FIX: fix miss on pcb and update gerber and schematic
2024-06-29 FEAT: add image description
2024-06-29 FEAT: add pinout description
2024-06-29 FEAT: add firmware
2024-06-29 FEAT: firmware setup based on base hardware
2024-07-01 DOC: add readme
2024-07-02 DOC: update status
2024-07-02 DOC: update doc
2024-07-02 FEAT : add compiled firmware
2024-07-17 FEAT: add dimension with case
2024-07-17 DOC: add image documentation
2024-07-17 FEAT: add 3d model
2024-07-17 FEAT: add 3d file case
2024-07-17 DOC: update readme add 3d case link
2024-11-29 FIX: fix wrong item , cap to res for pulldown the mosfet on psu source
2025-02-15 FEAT: update case after trial 1
2025-02-23 FEAT: ADD IMAGE REAL
2025-02-23 FEAT: add image on readme
2025-09-04 FEAT: testing for current PCB
2025-09-04 FEAT: add compiled firmware for BMI-160
2025-12-20 FEAT: update lasted customer wifi ssid"
2025-12-20 FEAT: add readme untuk penggunaan firmware
2025-12-20 FEAT: update readme

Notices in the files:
README.md:
License: MIT
parts and their libraries:
microbuilder: This work is placed in the public domain, and may be freely used for commercial and non-commercial work with the following conditions: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
COPYRIGHT: Copyright (C) 2016 Accelerated Designs. All rights reserved
